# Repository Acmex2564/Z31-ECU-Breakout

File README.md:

#Z31-ECU-Breakout

This repository contains KiCad files for a breakout board usable for the 1980s Nissan ECCS with the 36(20+16)+15 pin harness.

I used this to run an M30 ECU without chopping up my existing harness prior to fabricating a new 76-pin harness.

You will need a the 36-pin Dual-Line Interlock (DLI) header (AMP P/N 172023-1) and yet unidentified 15-pin header (looks kinda like a JPT/MCP part, marked for Mitsubishi Electric (SJB) but not in any English catalogs), and fasteners for both. The 15-pin header will need to be desoldered from a scrapped ECU; the 36-pin is available from Digikey/Mouser/etc. as of 2025.

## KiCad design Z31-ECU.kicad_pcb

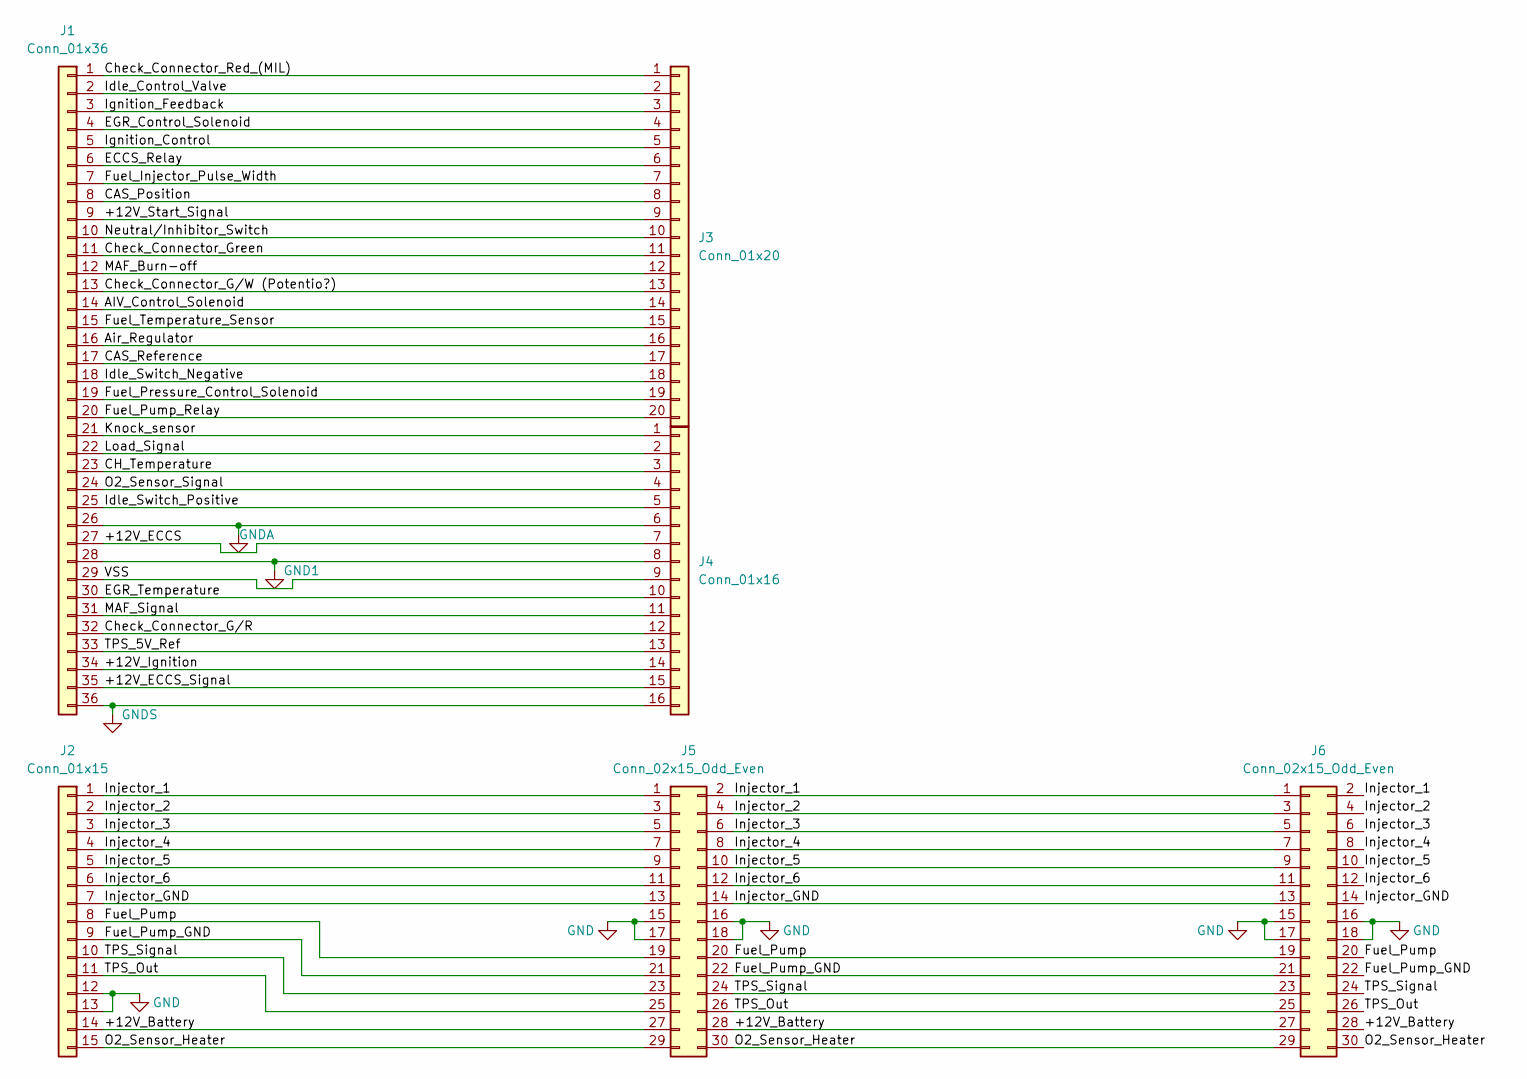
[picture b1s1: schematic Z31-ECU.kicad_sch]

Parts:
J1: Conn_01x36; TE-172023_Reverse_Number
J2: Conn_01x15; Z31_15p_ECU
J3: Conn_01x20; Z31_ECU_Breakout_2
J4: Conn_01x16; Z31_ECU_Breakout_1
J5, J6: Conn_02x15_Odd_Even; PinSocket_2x15_P2.54mm_Vertical

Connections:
/+12V_Battery: J2.14, J5.27, J5.28, J6.27, J6.28
/+12V_ECCS: J1.27, J4.7
/+12V_ECCS_Signal: J1.35, J4.15
/+12V_Ignition: J1.34, J4.14
/+12V_Start_Signal: J1.9, J3.9
/AIV_Control_Solenoid: J1.14, J3.14
/Air_Regulator: J1.16, J3.16
/CAS_Position: J1.8, J3.8
/CAS_Reference: J1.17, J3.17
/CH_Temperature: J1.23, J4.3
/Check_Connector_Green: J1.11, J3.11
/Check_Connector_G/R: J1.32, J4.12
/Check_Connector_G/W (Potentio?): J1.13, J3.13
/Check_Connector_Red_(MIL): J1.1, J3.1
/ECCS_Relay: J1.6, J3.6
/EGR_Control_Solenoid: J1.4, J3.4
/EGR_Temperature: J1.30, J4.10
/Fuel_Injector_Pulse_Width: J1.7, J3.7
/Fuel_Pressure_Control_Solenoid: J1.19, J3.19
/Fuel_Pump: J2.8, J5.19, J5.20, J6.19, J6.20
/Fuel_Pump_GND: J2.9, J5.21, J5.22, J6.21, J6.22
/Fuel_Pump_Relay: J1.20, J3.20
/Fuel_Temperature_Sensor: J1.15, J3.15
/Idle_Control_Valve: J1.2, J3.2
/Idle_Switch_Negative: J1.18, J3.18
/Idle_Switch_Positive: J1.25, J4.5
/Ignition_Control: J1.5, J3.5
/Ignition_Feedback: J1.3, J3.3
/Injector_1: J2.1, J5.1, J5.2, J6.1, J6.2
/Injector_2: J2.2, J5.3, J5.4, J6.3, J6.4
/Injector_3: J2.3, J5.5, J5.6, J6.5, J6.6
/Injector_4: J2.4, J5.7, J5.8, J6.7, J6.8
/Injector_5: J2.5, J5.9, J5.10, J6.9, J6.10
/Injector_6: J2.6, J5.11, J5.12, J6.11, J6.12
/Injector_GND: J2.7, J5.13, J5.14, J6.13, J6.14
/Knock_sensor: J1.21, J4.1
/Load_Signal: J1.22, J4.2
/MAF_Burn-off: J1.12, J3.12
/MAF_Signal: J1.31, J4.11
/Neutral/Inhibitor_Switch: J1.10, J3.10
/O2_Sensor_Heater: J2.15, J5.29, J5.30, J6.29, J6.30
/O2_Sensor_Signal: J1.24, J4.4
/TPS_5V_Ref: J1.33, J4.13
/TPS_Out: J2.11, J5.25, J5.26, J6.25, J6.26
/TPS_Signal: J2.10, J5.23, J5.24, J6.23, J6.24
/VSS: J1.29, J4.9
GND: J2.12, J2.13, J5.15, J5.16, J5.17, J5.18, J6.15, J6.16, J6.17, J6.18
GND1: J1.28, J4.8
GNDA: J1.26, J4.6
GNDS: J1.36, J4.16

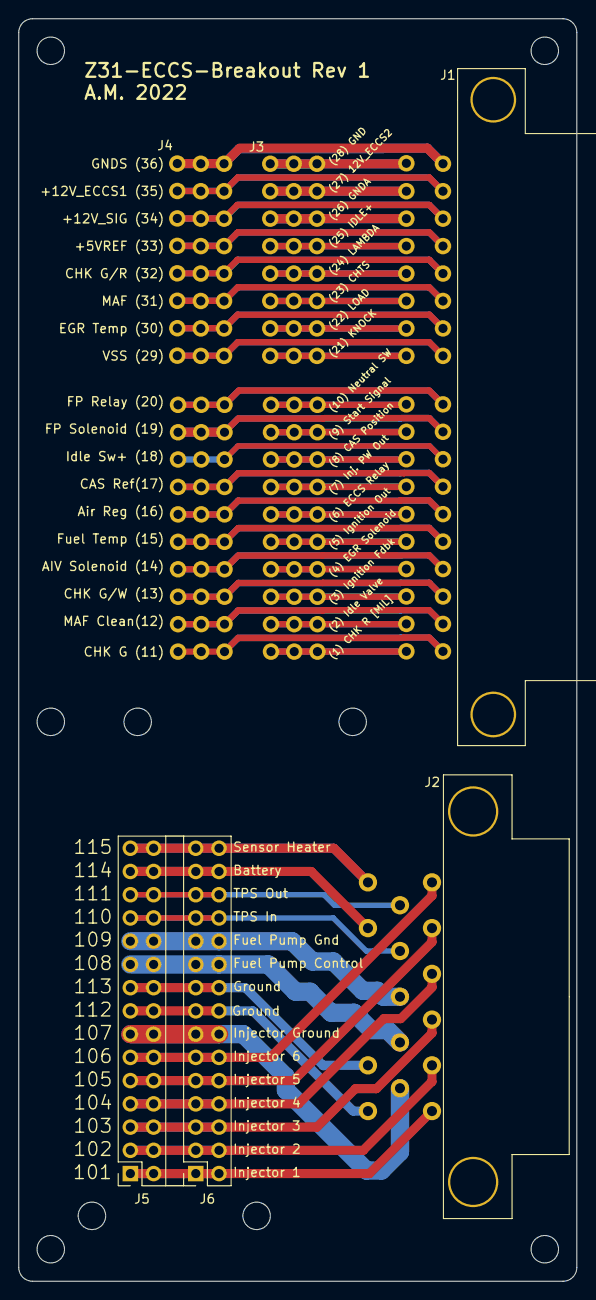
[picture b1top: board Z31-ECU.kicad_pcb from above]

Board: 2 copper layers, 61.0 x 138.0 mm, 6 parts (0 on the bottom side), 50 nets.

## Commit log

2025-03-21 Add Z31 ECCS breakout board files (useful reference)
2025-03-21 Add readme.md and KiCad renders of board
